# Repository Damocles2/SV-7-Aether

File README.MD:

****
## A revolutionary tool ##

The SV-7 is a small and lightweight handheld laser device, comprised of a 3d printed alluminium lower that serves as the device's heatsink and structure, as well as a pla cover that connects to it through a screwless assembly system.

Although it might look unasuming, it's tiny PCB is capable of providing up to 15w at a stable 5v with a single squeeze of it's pressure sensitive resistor

## Timeless design ##

The SV-7 might look simple at first glance, but a closer look will reveal that it's anything but. The design's attention to detail is showcased in the contrast between the smooth, beveled white, and the sleek metallic lower

And at only 18mm thick, it can easily fit in most large pockets

## Powerful and flexible hardware ##

The device's heart and brains are all contained within a tiny and highly dense pcb, fitting snugly within the device and effortlessly combining the high power/frequency power circuitry (boost converter,charger,high current transistor) with a highly flexible attiny chip, taking away the burden of having to stuff multiple modules inside of the elegant case, and allowing you to simply connect all 3 components and modify the resistor's sensitivity/safety features to your liking.

And with a 1a tp4056 charging IC, you can quickly charge it's 18650 or AA(A) cell with ease

## Simple yet modular ##

The metal base can support a wide range of laser and lenses depending on your needs. Although designed for 9mm lasers, the design can easily be changed to suit lower power 5.6mm lasers.

It also sports a carefully designed heatsink, designed to wick away the massive amounts of excess heat a powerful diode can produce

**⚠️ Alternatively, if the high cost of metal 3d printing isn't acceptable, both part can be produced with 3d printed polycarbonate, filled with mineral oil, and sealed. The diode mount can be hot glued to the top plastic to form a seal as not to have the oil affect the beam. ⚠️**

## Affordable ##

**Metal chassis**: <100$

**Top cover**: around 10 if you're having it printed online, otherwise <1$

**Populated PCB**: ~15$

**18650 battery** ~1.5$

**Collimating lens (optional):** ~1.99$ on aliexpress

**Trigger**: Any thin film pressure sensor would work if you set the right resistance. The sv-7 is designed for a long strip type unit (like the zd10-100), but a smaller circular one (eg: RP-C7.6-ST) is a far safer and more practical solution, if not quite as cool.

The device can be a little too front heavy for some users, so tungsten putty, available in most online marketplaces (eg: aliexpress) and fishing stores, can be added to the grip until an adequate balance is achieved.

The device itself should only cost about 125 dollars, however your price heavily depends on the diode you are using. I reccomend the SHARP GH04C05Y9G, which can be had on aliexpress for only 38.99$

This puts the total at a surprisingly low 140$ (with a metal chassis, see above for advice on producing plastic lower)

## A wide range of applications ##

As this is essentialy just a handheld laser diode with a comfortable grip, it can be used in various fields to perform a countless variety of tasks.

- Military use 
- Law enforcement use (for non lethal crowd control without a collimating lens)
- Self defence
- Engineering
- Mining (as a precision instrument)

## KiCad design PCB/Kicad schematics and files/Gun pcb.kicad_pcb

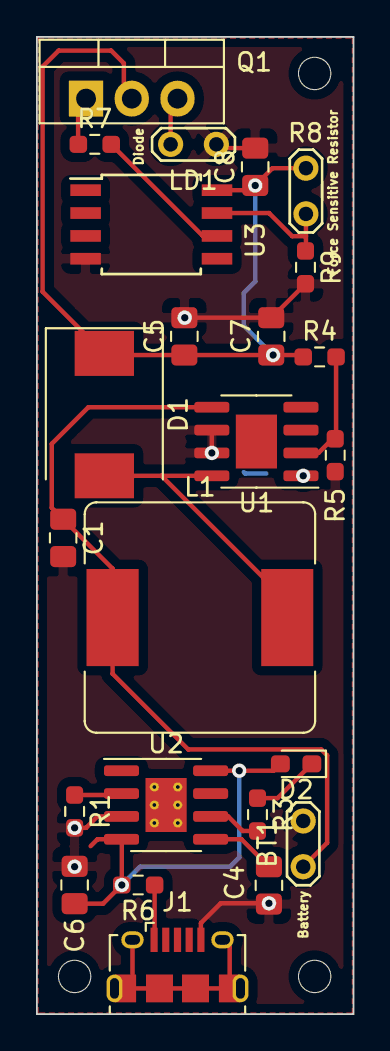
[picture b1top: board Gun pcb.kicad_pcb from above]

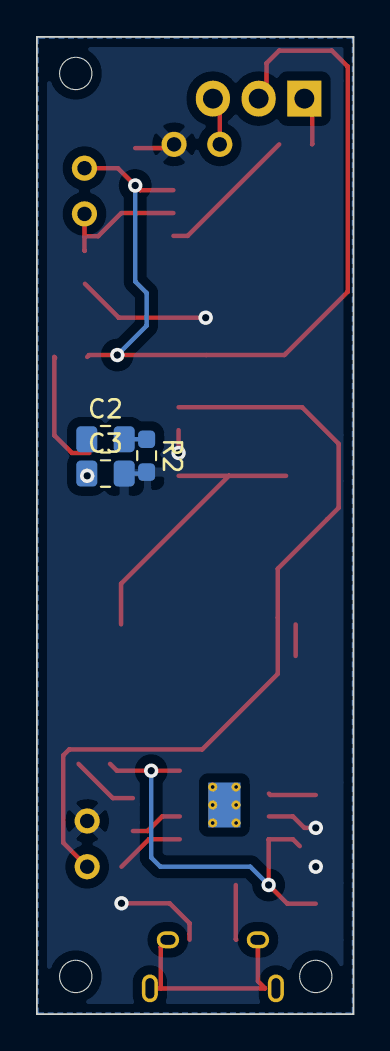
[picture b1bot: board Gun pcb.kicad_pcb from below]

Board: 2 copper layers, 17.6 x 54.3 mm, 27 parts (3 on the bottom side), 16 nets.

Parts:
BT1: Battery_Cell; TestPoint_2Pads_Pitch2.54mm_Drill0.8mm
C1, C5, C7: 22uF; C_0805_2012Metric_Pad1.18x1.45mm_HandSolder
C2, C8: 0.1uF; C_0805_2012Metric_Pad1.18x1.45mm_HandSolder
C3: 200pF; C_0805_2012Metric_Pad1.18x1.45mm_HandSolder
C4, C6: 10uF; C_0805_2012Metric_Pad1.18x1.45mm_HandSolder
D1: ss34; D_SMC
D2: LED; LED_0603_1608Metric_Pad1.05x0.95mm_HandSolder
J1: USB_B_Micro; USB_Micro-B_Amphenol_10118194_Horizontal
L1: 22uH; L_Bourns_SRR1260
LD1: High power laser diode; TestPoint_2Pads_Pitch2.54mm_Drill0.8mm
Q1: TIP120; TO-220-3_Vertical
R1: 1.2k; R_0603_1608Metric_Pad0.98x0.95mm_HandSolder
R2: 5k; R_0603_1608Metric_Pad0.98x0.95mm_HandSolder
R3: 1k; R_0603_1608Metric_Pad0.98x0.95mm_HandSolder
R4: 3.6k; R_0603_1608Metric_Pad0.98x0.95mm_HandSolder
R5: 1.3k; R_0603_1608Metric_Pad0.98x0.95mm_HandSolder
R6: 0.4 ohm; R_0603_1608Metric_Pad0.98x0.95mm_HandSolder
R7: 2.2k; R_0603_1608Metric_Pad0.98x0.95mm_HandSolder
R8: FSR; TestPoint_2Pads_Pitch2.54mm_Drill0.8mm
R9: 10k; R_0603_1608Metric_Pad0.98x0.95mm_HandSolder
U1: cs5171; SOIC-8-1EP_3.9x4.9mm_P1.27mm_EP2.29x3mm
U2: TP4056; SOIC-8-1EP_3.9x4.9mm_P1.27mm_EP2.29x3mm_ThermalVias
U3: ATtiny25-20SU; SOIJ-8_5.3x5.3mm_P1.27mm

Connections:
+5V: C5.1, C7.1, C8.1, D1.1, Q1.2, R4.1, R8.1, U3.8
+BATT: BT1.1, C1.1, C4.1, L1.1, U1.5, U2.5
GND: BT1.2, C1.2, C3.2, C4.2, C5.2, C6.2, C7.2, C8.2, J1.5, LD1.1, R1.2, R2.2, R5.2, R9.2, U1.6, U1.7, U2.3, U3.4
unnamed: C2.1, C3.1, U1.1
unnamed: C2.2, R2.1
unnamed: D1.2, L1.2, U1.8
unnamed: D2.1, R3.1
unnamed: LD1.2, Q1.3
unnamed: Q1.1, R7.1
unnamed: R1.1, U2.2
unnamed: R3.2, U2.6
unnamed: R4.2, R5.1, U1.2
unnamed: R8.2, R9.1, U3.7
VBUS: J1.1, R6.1
VCC: C6.1, D2.2, R6.2, U2.4, U2.8
laser: R7.2, U3.6

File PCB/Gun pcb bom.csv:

"Id";"Designator";"Package";"Quantity";"Designation";"Supplier and ref";
1;"BT1";"TestPoint_2Pads_Pitch2.54mm_Drill0.8mm";1;"Battery_Cell";;;
2;"C1,C5,C7";"C_0805_2012Metric_Pad1.18x1.45mm_HandSolder";3;"22uF";;;
3;"C2,C8";"C_0805_2012Metric_Pad1.18x1.45mm_HandSolder";2;"0.1uF";;;
4;"C3";"C_0805_2012Metric_Pad1.18x1.45mm_HandSolder";1;"200pF";;;
5;"C4,C6";"C_0805_2012Metric_Pad1.18x1.45mm_HandSolder";2;"10uF";;;
6;"D1";"D_SMC";1;"ss34";;;
7;"D2";"LED_0603_1608Metric_Pad1.05x0.95mm_HandSolder";1;"LED";;;
8;"J1";"USB_Micro-B_Amphenol_10118194_Horizontal";1;"USB_B_Micro";;;
9;"L1";"L_Bourns_SRR1260";1;"22uH";;;
10;"LD1";"TestPoint_2Pads_Pitch2.54mm_Drill0.8mm";1;"High power laser diode";;;
11;"Q1";"TO-220-3_Vertical";1;"TIP120";;;
12;"R1";"R_0603_1608Metric_Pad0.98x0.95mm_HandSolder";1;"1.2k";;;
13;"R2";"R_0603_1608Metric_Pad0.98x0.95mm_HandSolder";1;"5k";;;
14;"R3";"R_0603_1608Metric_Pad0.98x0.95mm_HandSolder";1;"1k";;;
15;"R4";"R_0603_1608Metric_Pad0.98x0.95mm_HandSolder";1;"3.6k";;;
16;"R5";"R_0603_1608Metric_Pad0.98x0.95mm_HandSolder";1;"1.3k";;;
17;"R6";"R_0603_1608Metric_Pad0.98x0.95mm_HandSolder";1;"0.4 ohm";;;
18;"R7";"R_0603_1608Metric_Pad0.98x0.95mm_HandSolder";1;"2.2k";;;
19;"R8";"TestPoint_2Pads_Pitch2.54mm_Drill0.8mm";1;"FSR";;;
20;"R9";"R_0603_1608Metric_Pad0.98x0.95mm_HandSolder";1;"10k";;;
21;"U1";"SOIC-8-1EP_3.9x4.9mm_P1.27mm_EP2.29x3mm";1;"cs5171";;;
22;"U2";"SOIC-8-1EP_3.9x4.9mm_P1.27mm_EP2.29x3mm_ThermalVias";1;"TP4056";;;
23;"U3";"SOIJ-8_5.3x5.3mm_P1.27mm";1;"ATtiny25-20SU";;;
